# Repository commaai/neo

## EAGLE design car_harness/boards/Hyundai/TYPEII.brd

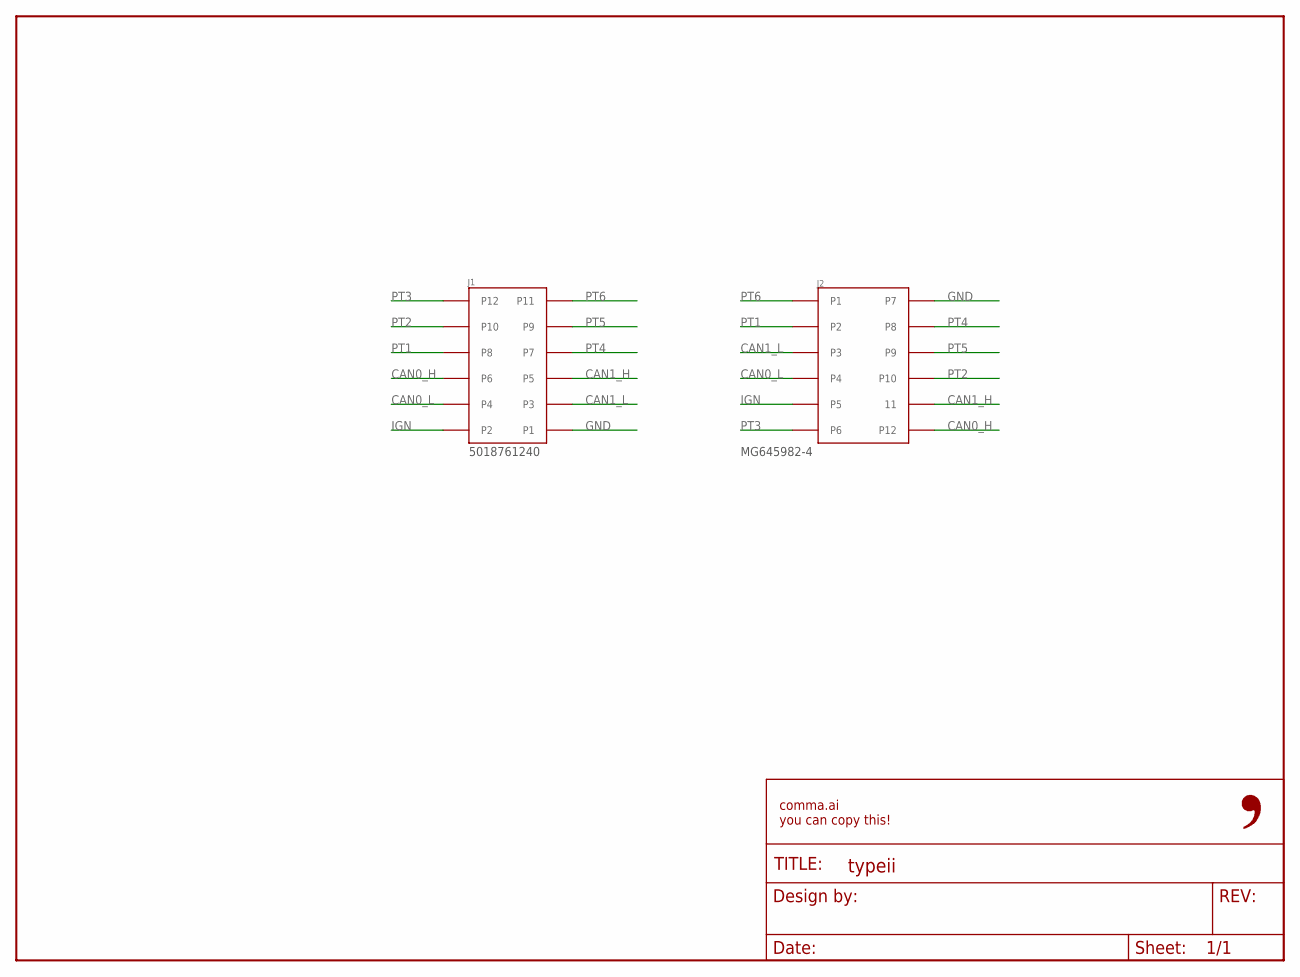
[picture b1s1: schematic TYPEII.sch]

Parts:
FRAME1: FRAME-LETTER-OPENNO_PACKAGE; DUMMY
J1: 5018761240; MPN 5018761240
J2: MG645845; MPN MG645845

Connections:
CAN0_H: J1.P6, J2.P12
CAN0_L: J1.P4, J2.P4
CAN1_H: J1.P5, J2.P11 (11)
CAN1_L: J1.P3, J2.P3
GND: J1.P1, J2.P7
IGN: J1.P2, J2.P5
PT1: J1.P8, J2.P2
PT2: J1.P10, J2.P10
PT3: J1.P12, J2.P6
PT4: J1.P7, J2.P8
PT5: J1.P9, J2.P9
PT6: J1.P11, J2.P1

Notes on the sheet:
MG645982-4
5018761240

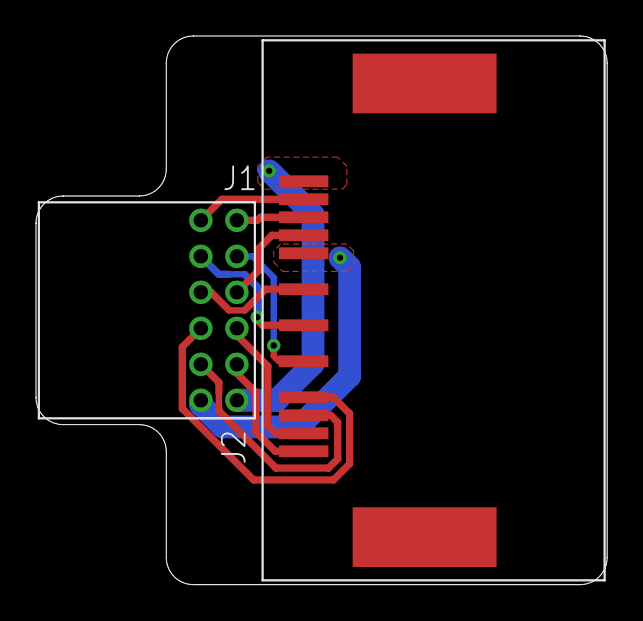
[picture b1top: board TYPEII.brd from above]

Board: 2 copper layers, 31.7 x 30.5 mm, 4 parts (1 on the bottom side), 12 nets.

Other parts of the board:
U$1: LOGO

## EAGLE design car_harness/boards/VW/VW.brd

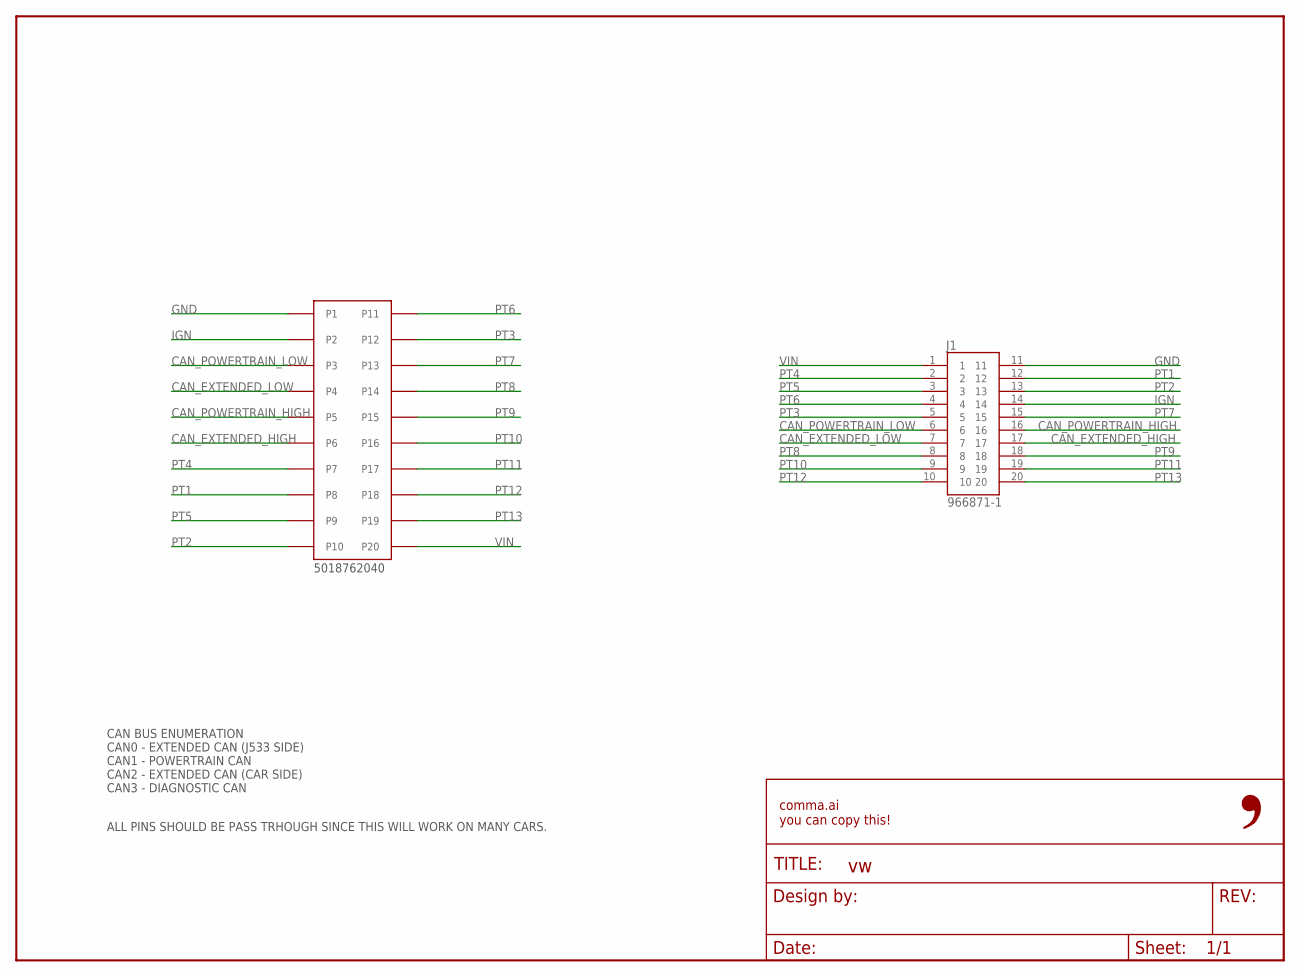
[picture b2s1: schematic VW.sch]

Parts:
FRAME1: FRAME-LETTER-OPENNO_PACKAGE; DUMMY
J1: 966871-1; TE_966871-1; MPN 966871-1
J2: 5018762040; MPN 5018762040

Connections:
CAN_EXTENDED_HIGH: J1.17, J2.P6
CAN_EXTENDED_LOW: J1.7, J2.P4
CAN_POWERTRAIN_HIGH: J1.16, J2.P5
CAN_POWERTRAIN_LOW: J1.6, J2.P3
GND: J1.11, J2.P1
IGN: J1.14, J2.P2
PT1: J1.12, J2.P8
PT2: J1.13, J2.P10
PT3: J1.5, J2.P12
PT4: J1.2, J2.P7
PT5: J1.3, J2.P9
PT6: J1.4, J2.P11
PT7: J1.15, J2.P13
PT8: J1.8, J2.P14
PT9: J1.18, J2.P15
PT10: J1.9, J2.P16
PT11: J1.19, J2.P17
PT12: J1.10, J2.P18
PT13: J1.20, J2.P19
VIN: J1.1, J2.P20

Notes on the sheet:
CAN BUS ENUMERATION CAN0 - EXTENDED CAN (J533 SIDE) CAN1 - POWERTRAIN CAN CAN2 - EXTENDED CAN (CAR SIDE) CAN3 - DIAGNOSTIC CAN
ALL PINS SHOULD BE PASS TRHOUGH SINCE THIS WILL WORK ON MANY CARS.
5018762040

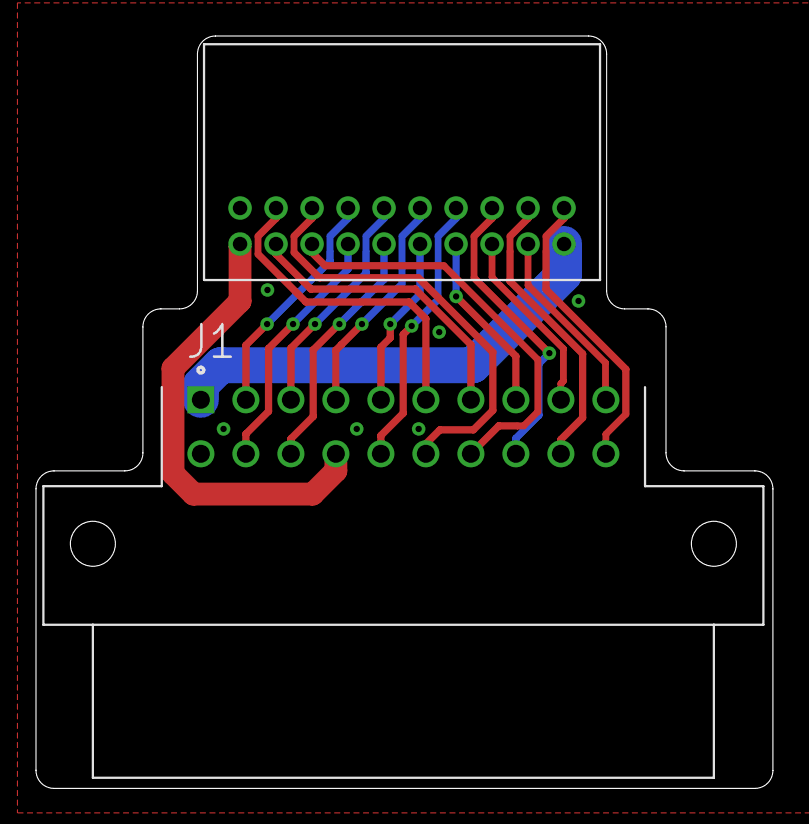
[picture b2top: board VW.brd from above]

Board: 2 copper layers, 40.9 x 41.8 mm, 4 parts (1 on the bottom side), 20 nets.

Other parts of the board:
U$1: LOGO

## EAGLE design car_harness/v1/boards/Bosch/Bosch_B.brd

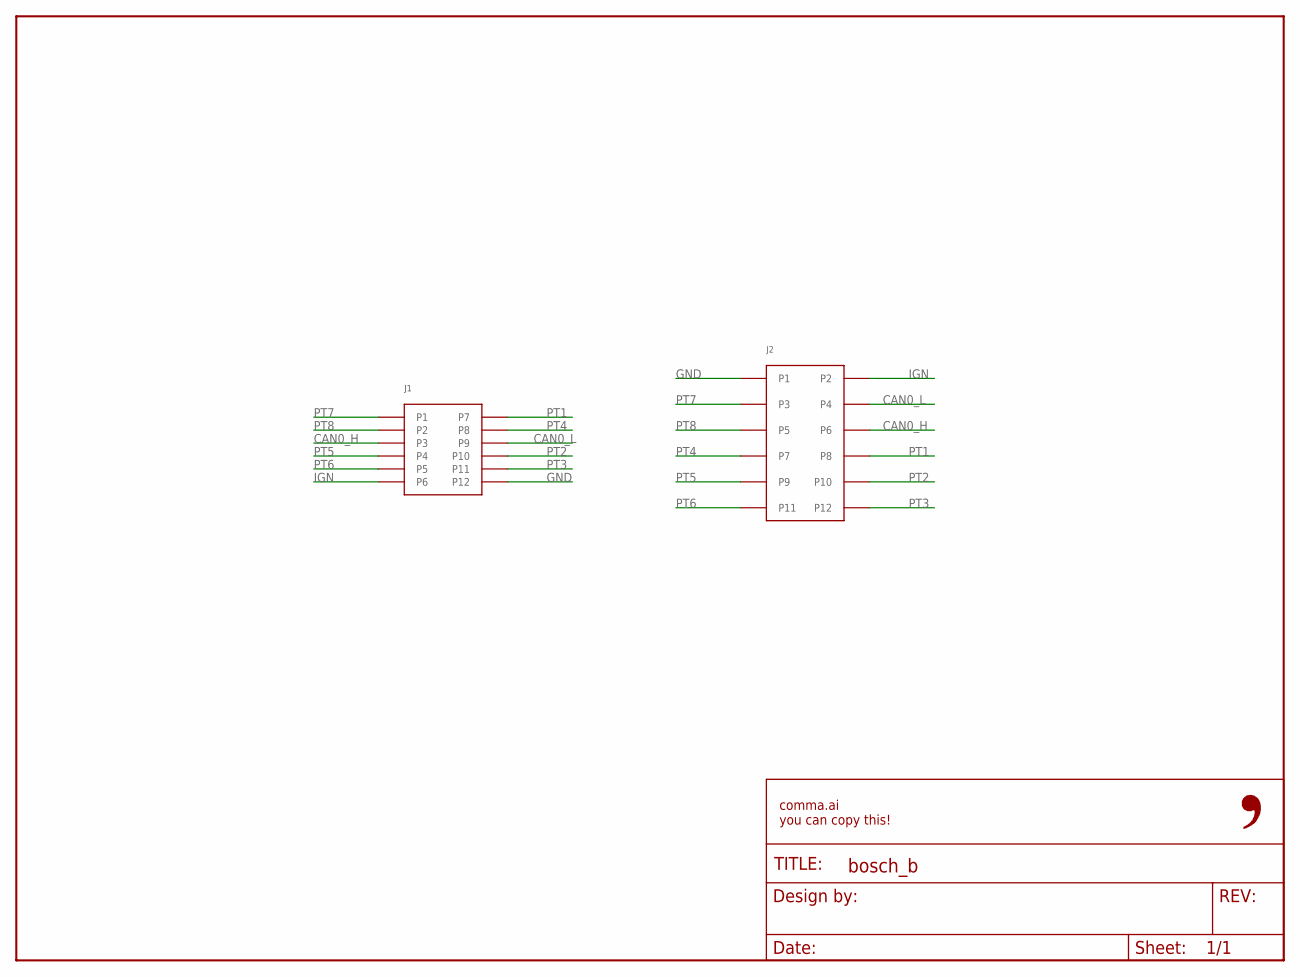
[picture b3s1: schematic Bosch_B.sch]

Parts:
FRAME1: FRAME-LETTER-OPENNO_PACKAGE; DUMMY
J1: MX34M12NF1; MPN MX34M12NF1
J2: 5018761240; MPN 5018761240

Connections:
CAN0_H: J1.P3, J2.P6
CAN0_L: J1.P9, J2.P4
GND: J1.P12, J2.P1
IGN: J1.P6, J2.P2
PT1: J1.P7, J2.P8
PT2: J1.P10, J2.P10
PT3: J1.P11, J2.P12
PT4: J1.P8, J2.P7
PT5: J1.P4, J2.P9
PT6: J1.P5, J2.P11
PT7: J1.P1, J2.P3
PT8: J1.P2, J2.P5

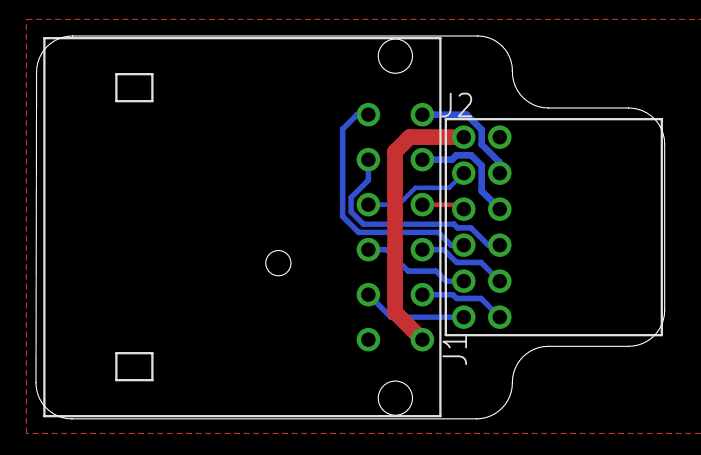
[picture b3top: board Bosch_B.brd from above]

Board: 2 copper layers, 34.9 x 21.3 mm, 4 parts (1 on the bottom side), 12 nets.

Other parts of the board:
E$1: LOGO

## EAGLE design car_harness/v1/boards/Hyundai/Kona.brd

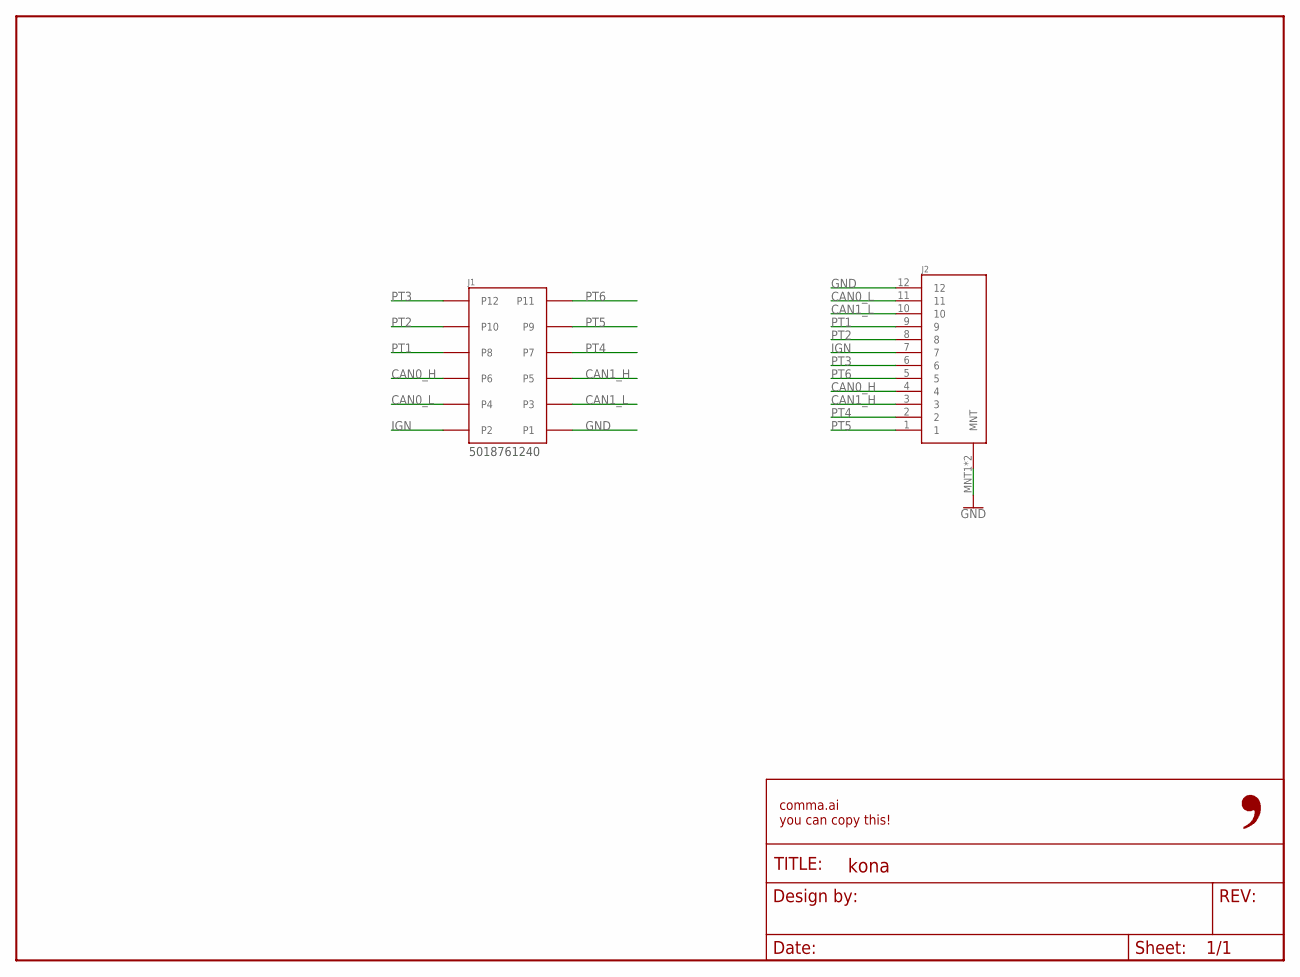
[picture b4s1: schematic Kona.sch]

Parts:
FRAME1: FRAME-LETTER-OPENNO_PACKAGE; DUMMY
J1: 5018761240; MPN 5018761240
J2: MG646151; MPN MG646151-5

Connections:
CAN0_H: J1.P6, J2.4
CAN0_L: J1.P4, J2.11
CAN1_H: J1.P5, J2.3
CAN1_L: J1.P3, J2.10
GND: J1.P1, J2.12, J2.MNT1 (MNT), J2.MNT2 (MNT)
IGN: J1.P2, J2.7
PT1: J1.P8, J2.9
PT2: J1.P10, J2.8
PT3: J1.P12, J2.6
PT4: J1.P7, J2.2
PT5: J1.P9, J2.1
PT6: J1.P11, J2.5

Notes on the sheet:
5018761240

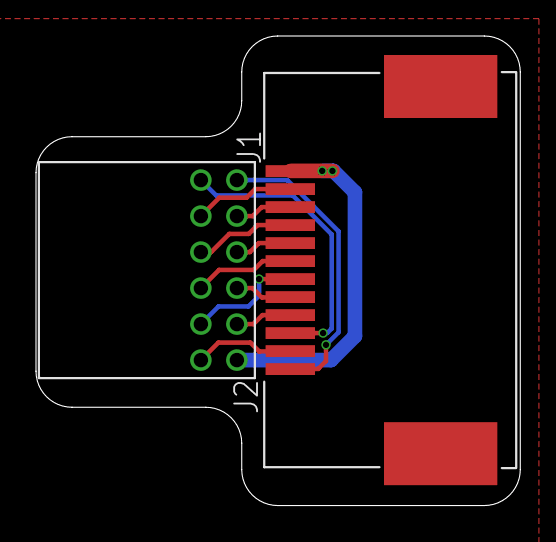
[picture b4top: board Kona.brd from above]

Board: 2 copper layers, 26.9 x 26.1 mm, 4 parts (1 on the bottom side), 12 nets.

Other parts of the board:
U$1: LOGO

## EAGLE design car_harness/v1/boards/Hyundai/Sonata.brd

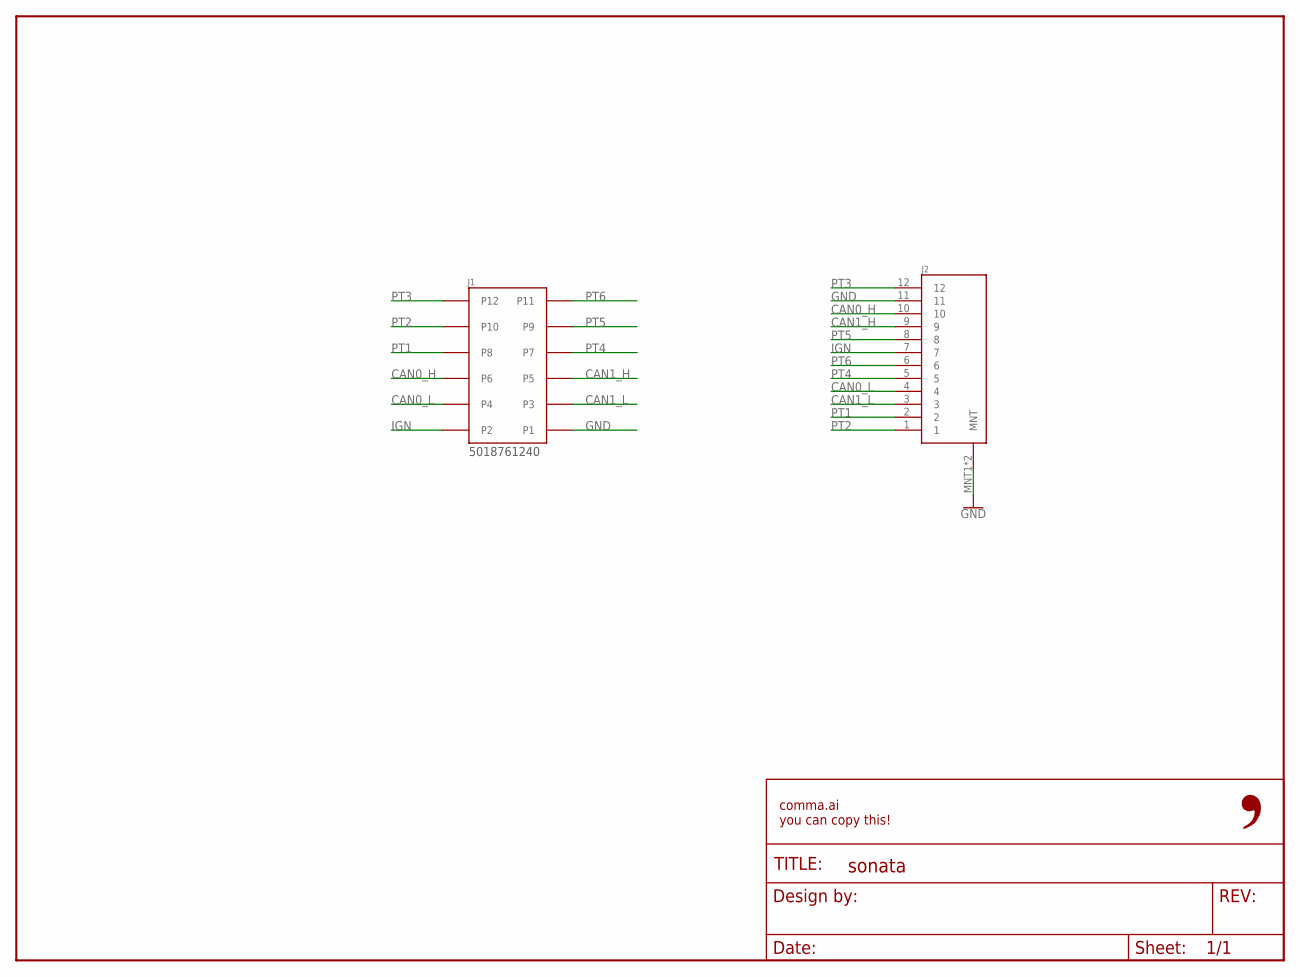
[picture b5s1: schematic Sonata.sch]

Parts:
FRAME1: FRAME-LETTER-OPENNO_PACKAGE; DUMMY
J1: 5018761240; MPN 5018761240
J2: MG646151; MPN MG646151-5

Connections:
CAN0_H: J1.P6, J2.10
CAN0_L: J1.P4, J2.4
CAN1_H: J1.P5, J2.9
CAN1_L: J1.P3, J2.3
GND: J1.P1, J2.11, J2.MNT1 (MNT), J2.MNT2 (MNT)
IGN: J1.P2, J2.7
PT1: J1.P8, J2.2
PT2: J1.P10, J2.1
PT3: J1.P12, J2.12
PT4: J1.P7, J2.5
PT5: J1.P9, J2.8
PT6: J1.P11, J2.6

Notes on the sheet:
5018761240

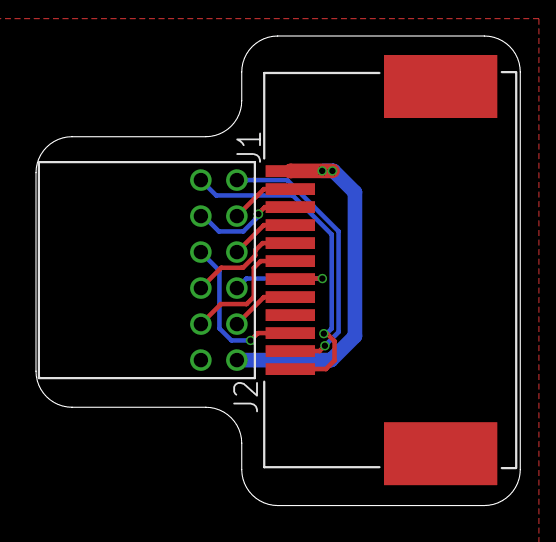
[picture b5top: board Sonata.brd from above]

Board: 2 copper layers, 26.9 x 26.1 mm, 4 parts (1 on the bottom side), 12 nets.

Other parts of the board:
U$1: LOGO

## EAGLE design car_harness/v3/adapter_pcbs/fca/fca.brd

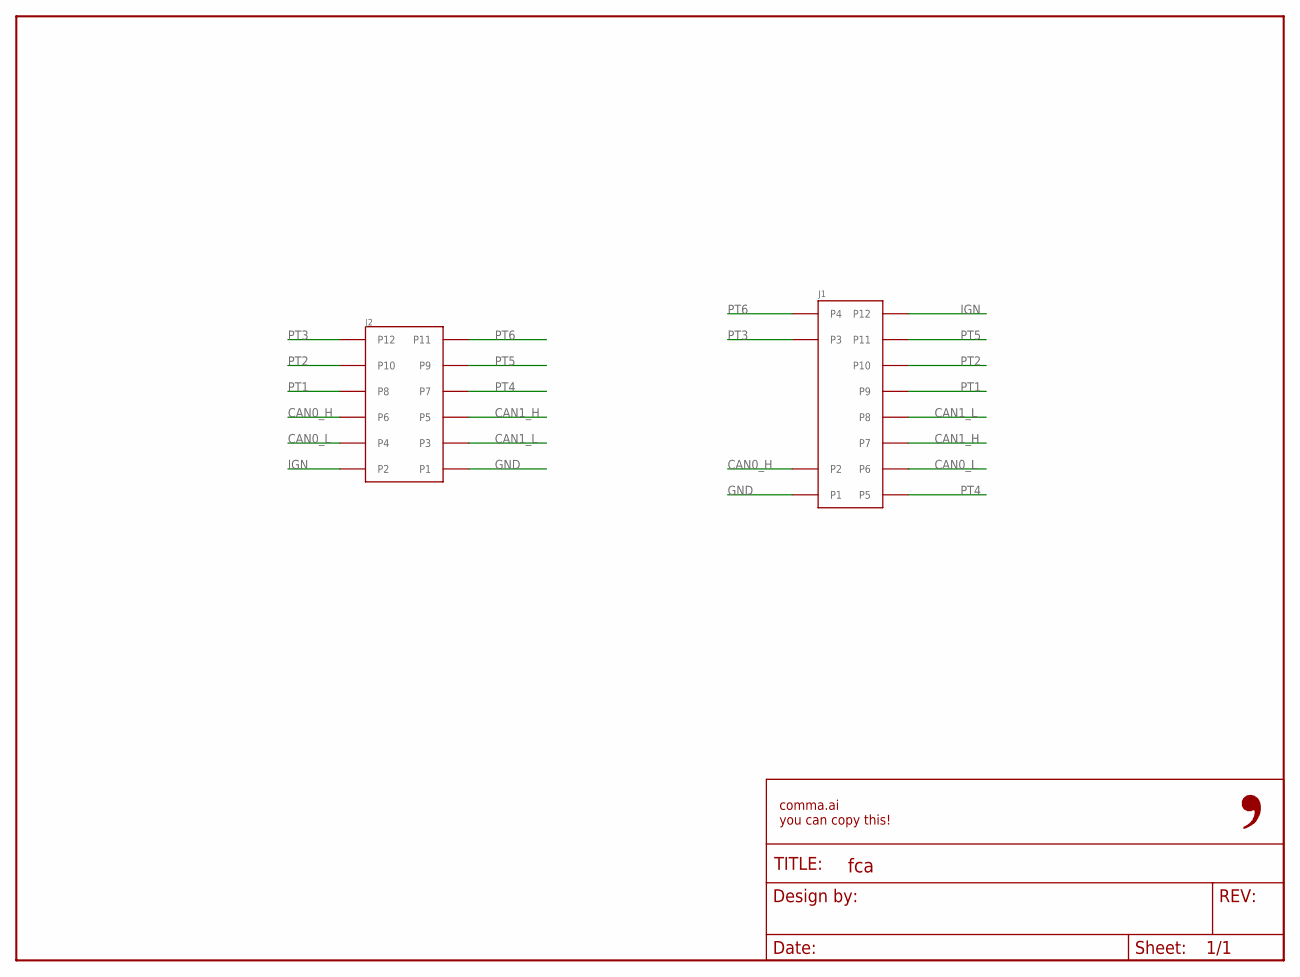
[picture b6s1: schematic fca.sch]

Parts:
FRAME1: FRAME-LETTER-OPENNO_PACKAGE; DUMMY
J1: 0348260124
J2: 5018761240

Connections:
CAN0_H: J1.P2, J2.P6
CAN0_L: J1.P6, J2.P4
CAN1_H: J1.P7, J2.P5
CAN1_L: J1.P8, J2.P3
GND: J1.P1, J2.P1
IGN: J1.P12, J2.P2
PT1: J1.P9, J2.P8
PT2: J1.P10, J2.P10
PT3: J1.P3, J2.P12
PT4: J1.P5, J2.P7
PT5: J1.P11, J2.P9
PT6: J1.P4, J2.P11

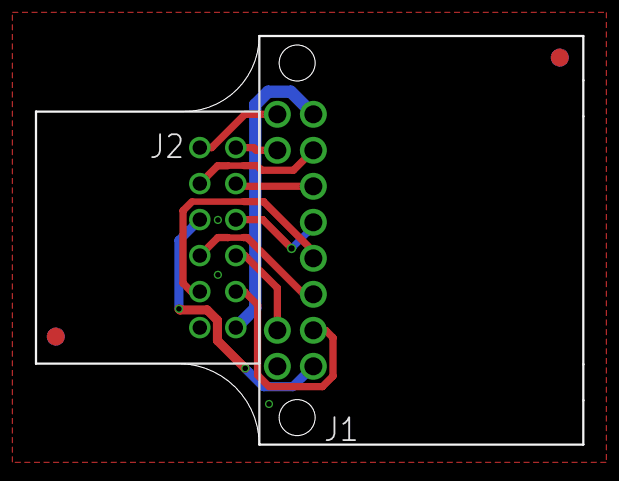
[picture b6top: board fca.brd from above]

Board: 2 copper layers, 30.4 x 22.7 mm, 6 parts (1 on the bottom side), 12 nets.

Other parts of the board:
U$1: LOGO
U$2, U$3: FIDUCIAL

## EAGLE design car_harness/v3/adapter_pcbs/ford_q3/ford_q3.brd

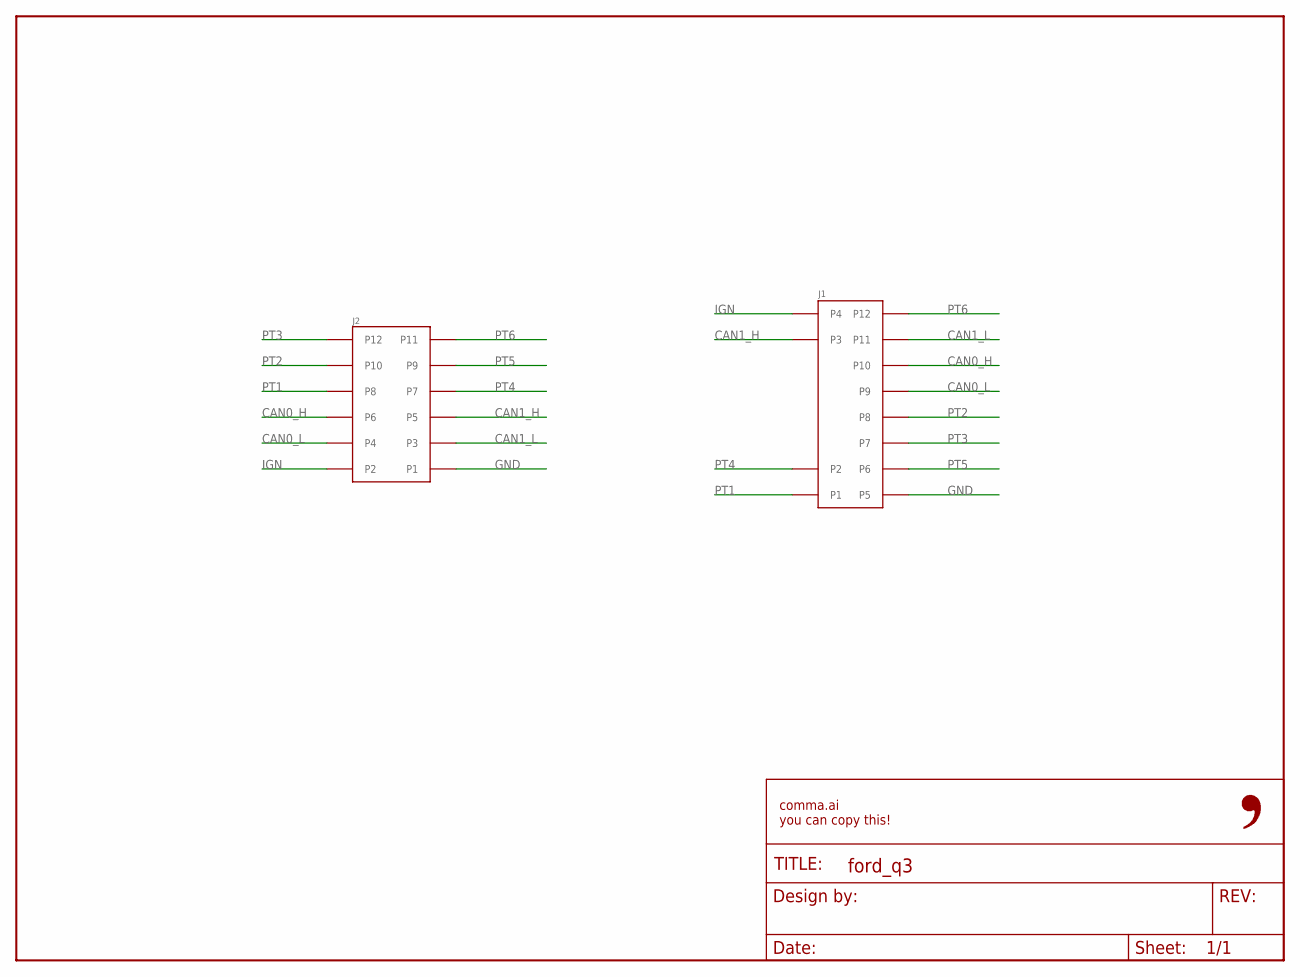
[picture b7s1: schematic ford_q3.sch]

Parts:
FRAME1: FRAME-LETTER-OPENNO_PACKAGE; DUMMY
J1: 0348260124
J2: 5018761240

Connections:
CAN0_H: J1.P10, J2.P6
CAN0_L: J1.P9, J2.P4
CAN1_H: J1.P3, J2.P5
CAN1_L: J1.P11, J2.P3
GND: J1.P5, J2.P1
IGN: J1.P4, J2.P2
PT1: J1.P1, J2.P8
PT2: J1.P8, J2.P10
PT3: J1.P7, J2.P12
PT4: J1.P2, J2.P7
PT5: J1.P6, J2.P9
PT6: J1.P12, J2.P11

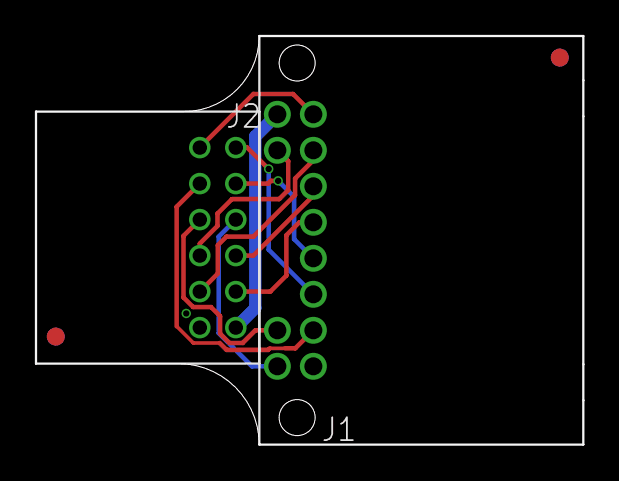
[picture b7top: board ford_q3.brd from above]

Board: 2 copper layers, 30.4 x 22.7 mm, 6 parts (1 on the bottom side), 12 nets.

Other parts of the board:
U$1: LOGO
U$2, U$3: FIDUCIAL
